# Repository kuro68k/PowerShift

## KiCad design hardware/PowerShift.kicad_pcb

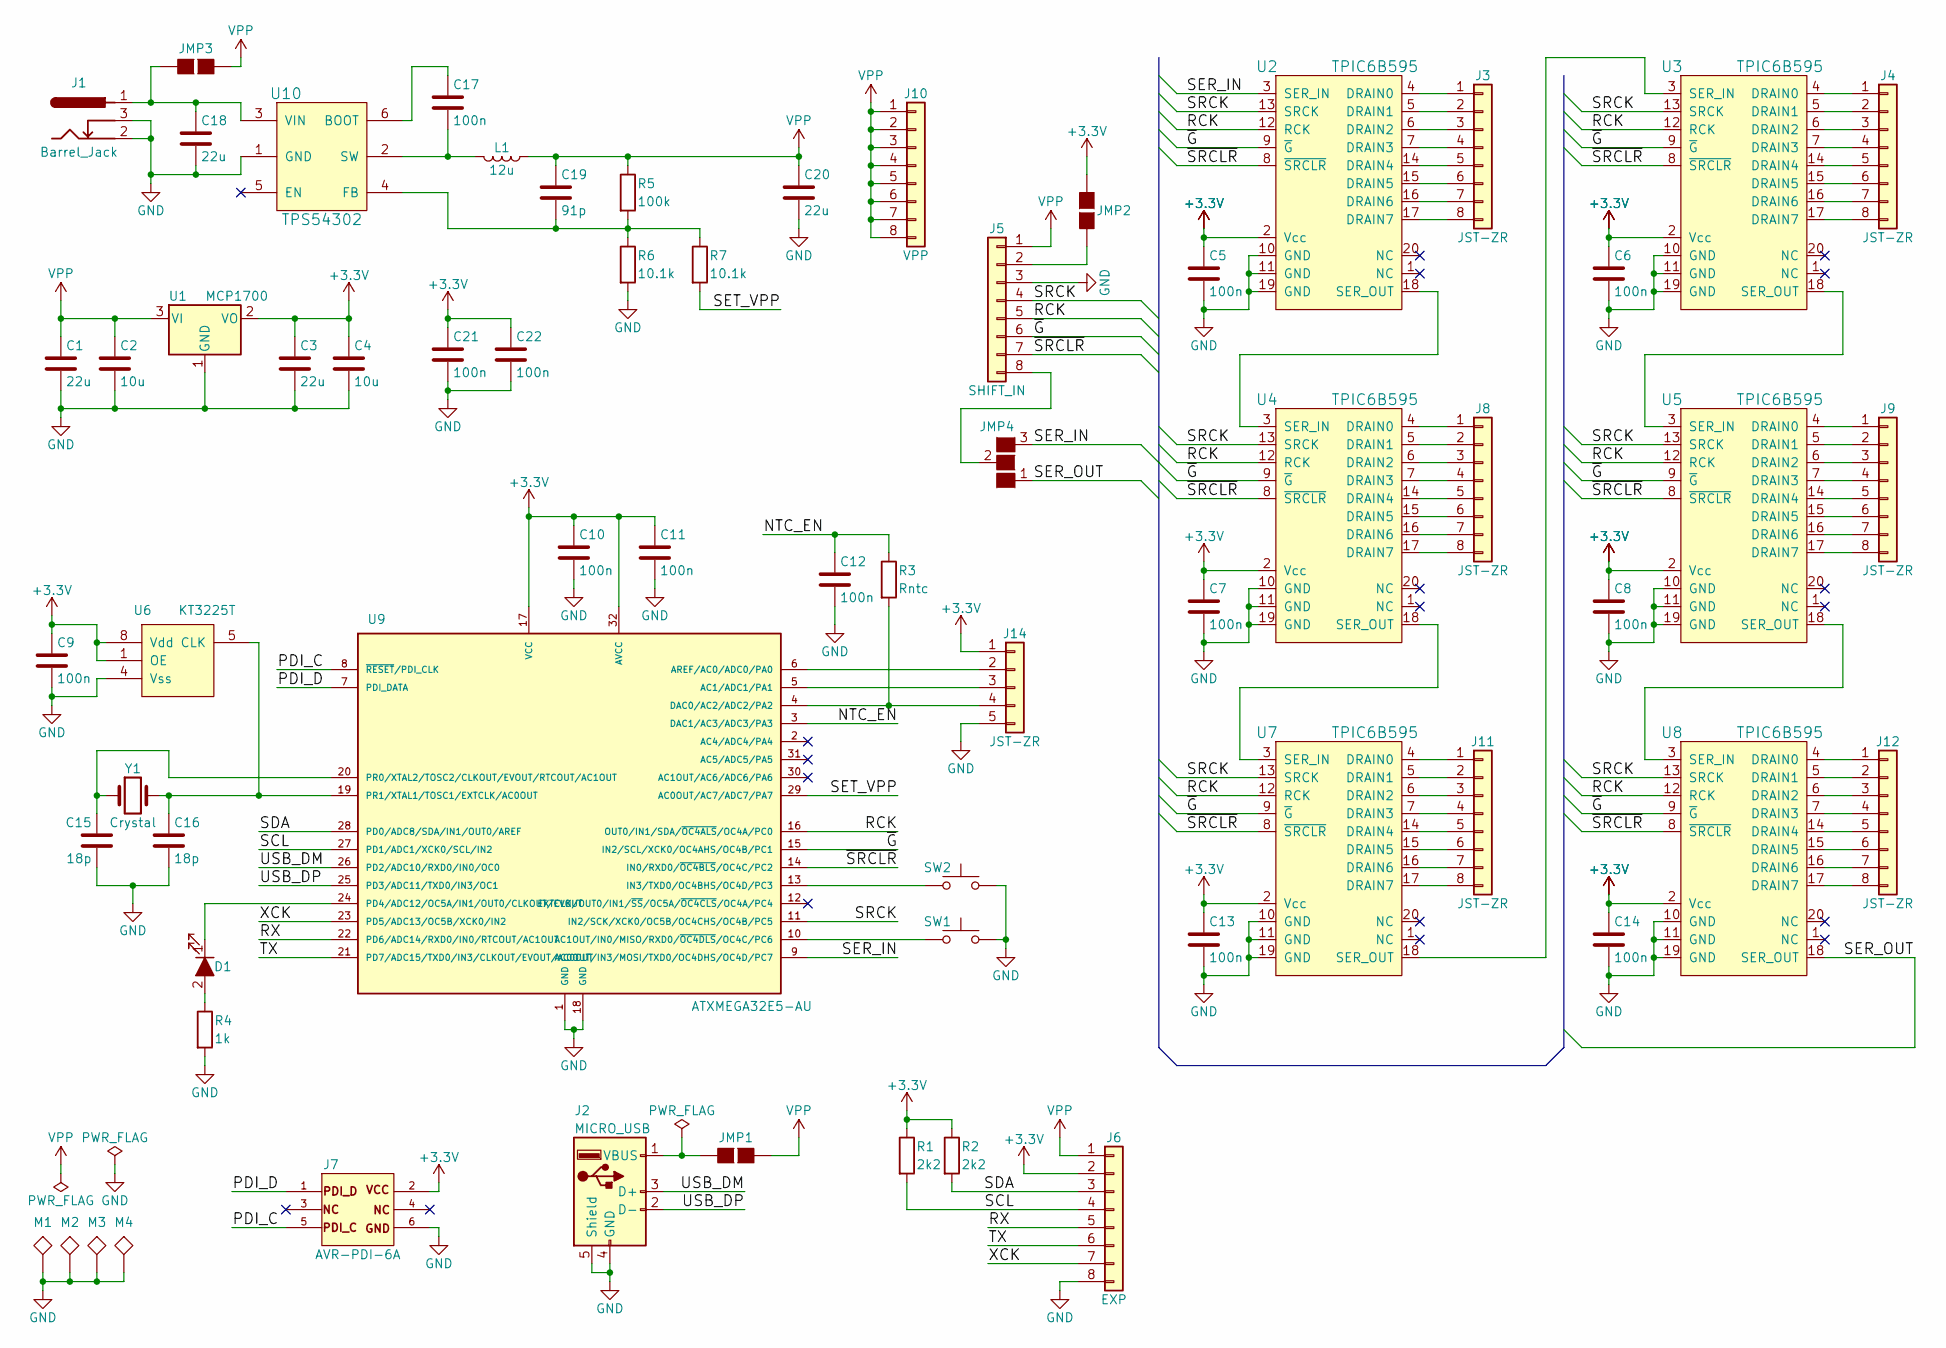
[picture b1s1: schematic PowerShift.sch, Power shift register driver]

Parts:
C1, C3, C18, C20: 22u; C_0805_HandSoldering
C2, C4: 10u; C_0603_HandSoldering
C5, C6, C7, C8, C9, C10, C11, C12, C13, C14, C17, C21, C22: 100n; C_0603_HandSoldering
C15, C16: 18p; C_0603_HandSoldering
C19: 91p; C_0603_HandSoldering
D1: LED_ALT; LED_0603_HandSoldering
J1: Barrel_Jack; DC_Jack_SMD_FC6814xS_6941
J2: MICRO_USB; Molex_47346-0001_Micro_USB_SMT
J3, J4, J8, J9, J11, J12: JST-ZR; B8B-ZR-SM4-TF
J5: SHIFT_IN; Pin_Header_Straight_1x08_Pitch2.54mm
J6: EXP; B8B-ZR-SM4-TF
J7: AVR-PDI-6A; Pin_Header_Angled_2x03_Pitch2.54mm
J10: VPP; B8B-ZR-SM4-TF
J14: JST-ZR; B5B-ZR-SM4-TF
JMP1, JMP2, JMP3: GS2
JMP4: GS3
L1: 12u; Bourns_SDR1307_14x14mm
M1, M2, M3, M4: TEST; MountingHole_2.7mm_M2.5_Pad
R1, R2: 2k2; R_0603_HandSoldering
R3: Rntc; R_0603_HandSoldering
R4: 1k; R_0603_HandSoldering
R5: 100k; R_0603_HandSoldering
R6, R7: 10.1k; R_0603_HandSoldering
SW1, SW2: SW_Push; Switch_FSM-JSM-Series
U1: MCP1700; SOT-23
U2, U3, U4, U5, U7, U8: TPIC6B595; SOIC-20W_7.5x12.8mm_Pitch1.27mm
U6: KT3225T
U9: ATXMEGA32E5-AU; TQFP-32_7x7mm_Pitch0.8mm
U10: TPS54302; SOT-23-6_Handsoldering
Y1: Crystal; Crystal_2pin_6x3.5_3.2x1.5_Multi

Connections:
+3V3: C3.1, C4.1, C5.1, C6.1, C7.1, C8.1, C9.1, C10.1, C11.1, C13.1, C14.1, C21.1, C22.1, J6.2, J7.2, J14.1, JMP2.1 (G1), R1.1, R2.1, U1.2 (VO), U2.2 (Vcc), U3.2 (Vcc), U4.2 (Vcc), U5.2 (Vcc), U6.1 (OE), U6.8 (Vdd), U7.2 (Vcc), U8.2 (Vcc), U9.17 (VCC), U9.32 (AVCC)
/NTC_EN: C12.1, R3.1, U9.3 (DAC1/AC3/ADC3/PA3)
/PDI_C: J7.5, U9.8 (~RESET~/PDI_CLK)
/PDI_D: J7.1, U9.7 (PDI_DATA)
/RCK: J5.5, U2.12 (RCK), U3.12 (RCK), U4.12 (RCK), U5.12 (RCK), U7.12 (RCK), U8.12 (RCK), U9.16 (OUT0/IN1/SDA/~OC4ALS~/OC4A/PC0)
/RX: J6.5, U9.22 (PD6/ADC14/RXD0/IN0/RTCOUT/AC1OUT)
/SCL: J6.4, R1.2, U9.27 (PD1/ADC1/XCK0/SCL/IN2)
/SDA: J6.3, R2.2, U9.28 (PD0/ADC8/SDA/IN1/OUT0/AREF)
/SER_IN: JMP4.3 (G3), U2.3 (SER_IN), U9.9 (AC0OUT/IN3/MOSI/TXD0/OC4DHS/OC4D/PC7)
/SER_OUT: JMP4.1 (G1), U8.18 (SER_OUT)
/SET_VPP: R7.2, U9.29 (AC0OUT/AC7/ADC7/PA7)
/SRCK: J5.4, U2.13 (SRCK), U3.13 (SRCK), U4.13 (SRCK), U5.13 (SRCK), U7.13 (SRCK), U8.13 (SRCK), U9.11 (IN2/SCK/XCK0/OC5B/OC4CHS/OC4B/PC5)
/TX: J6.6, U9.21 (PD7/ADC15/TXD0/IN3/CLKOUT/EVOUT/AC0OUT)
/USB_DM: J2.3 (D+), U9.26 (PD2/ADC10/RXD0/IN0/OC0)
/USB_DP: J2.2 (D-), U9.25 (PD3/ADC11/TXD0/IN3/OC1)
/XCK: J6.7, U9.23 (PD5/ADC13/OC5B/XCK0/IN2)
/~G: J5.6, U2.9 (~G), U3.9 (~G), U4.9 (~G), U5.9 (~G), U7.9 (~G), U8.9 (~G), U9.15 (IN2/SCL/XCK0/OC4AHS/OC4B/PC1)
/~SRCLR: J5.7, U2.8 (~SRCLR), U3.8 (~SRCLR), U4.8 (~SRCLR), U5.8 (~SRCLR), U7.8 (~SRCLR), U8.8 (~SRCLR), U9.14 (IN0/RXD0/~OC4BLS~/OC4C/PC2)
GND: C1.2, C2.2, C3.2, C4.2, C5.2, C6.2, C7.2, C8.2, C9.2, C10.2, C11.2, C12.2, C13.2, C14.2, C15.2, C16.2, C18.2, C20.2, C21.2, C22.2, J1.2, J1.3, J2.4 (GND), J2.5 (Shield), J5.3, J6.8, J7.6, J14.5, M1.1, M2.1, M3.1, M4.1, R4.2, R6.2, SW1.1, SW2.1, U1.1 (GND), U2.10 (GND), U2.11 (GND), U2.19 (GND), U3.10 (GND), U3.11 (GND), U3.19 (GND), U4.10 (GND), U4.11 (GND), U4.19 (GND), U5.10 (GND), U5.11 (GND), U5.19 (GND), U6.4 (Vss), U7.10 (GND), U7.11 (GND), U7.19 (GND), U8.10 (GND), U8.11 (GND), U8.19 (GND), U9.1 (GND), U9.18 (GND), U10.1 (GND)
unnamed: C15.1, U9.20 (PR0/XTAL2/TOSC2/CLKOUT/EVOUT/RTCOUT/AC1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), Y1.1
unnamed: C16.1, U6.5 (CLK), U9.19 (PR1/XTAL1/TOSC1/EXTCLK/AC0OUT), Y1.2
unnamed: C17.1, U10.6 (BOOT)
unnamed: C17.2, L1.2, U10.2 (SW)
unnamed: C18.1, J1.1, JMP3.1 (G1), U10.3 (VIN)
unnamed: C19.2, R5.2, R6.1, R7.1, U10.4 (FB)
unnamed: D1.1 (K), U9.24 (PD4/ADC12/OC5A/IN1/OUT0/CLKOUT/EVOUT)
unnamed: D1.2 (A), R4.1
unnamed: J2.1 (VBUS), JMP1.1 (G1)
unnamed: J3.1, U2.4 (DRAIN0)
unnamed: J3.2, U2.5 (DRAIN1)
unnamed: J3.3, U2.6 (DRAIN2)
unnamed: J3.4, U2.7 (DRAIN3)
unnamed: J3.5, U2.14 (DRAIN4)
unnamed: J3.6, U2.15 (DRAIN5)
unnamed: J3.7, U2.16 (DRAIN6)
unnamed: J3.8, U2.17 (DRAIN7)
unnamed: J4.1, U3.4 (DRAIN0)
unnamed: J4.2, U3.5 (DRAIN1)
unnamed: J4.3, U3.6 (DRAIN2)
unnamed: J4.4, U3.7 (DRAIN3)
unnamed: J4.5, U3.14 (DRAIN4)
unnamed: J4.6, U3.15 (DRAIN5)
unnamed: J4.7, U3.16 (DRAIN6)
unnamed: J4.8, U3.17 (DRAIN7)
unnamed: J5.2, JMP2.2 (G2)
unnamed: J5.8, JMP4.2 (G2)
unnamed: J8.1, U4.4 (DRAIN0)
unnamed: J8.2, U4.5 (DRAIN1)
unnamed: J8.3, U4.6 (DRAIN2)
unnamed: J8.4, U4.7 (DRAIN3)
unnamed: J8.5, U4.14 (DRAIN4)
unnamed: J8.6, U4.15 (DRAIN5)
unnamed: J8.7, U4.16 (DRAIN6)
unnamed: J8.8, U4.17 (DRAIN7)
unnamed: J9.1, U5.4 (DRAIN0)
unnamed: J9.2, U5.5 (DRAIN1)
unnamed: J9.3, U5.6 (DRAIN2)
unnamed: J9.4, U5.7 (DRAIN3)
unnamed: J9.5, U5.14 (DRAIN4)
unnamed: J9.6, U5.15 (DRAIN5)
unnamed: J9.7, U5.16 (DRAIN6)
unnamed: J9.8, U5.17 (DRAIN7)
unnamed: J11.1, U7.4 (DRAIN0)
unnamed: J11.2, U7.5 (DRAIN1)
unnamed: J11.3, U7.6 (DRAIN2)
unnamed: J11.4, U7.7 (DRAIN3)
unnamed: J11.5, U7.14 (DRAIN4)
unnamed: J11.6, U7.15 (DRAIN5)
unnamed: J11.7, U7.16 (DRAIN6)
unnamed: J11.8, U7.17 (DRAIN7)
unnamed: J12.1, U8.4 (DRAIN0)
unnamed: J12.2, U8.5 (DRAIN1)
unnamed: J12.3, U8.6 (DRAIN2)
unnamed: J12.4, U8.7 (DRAIN3)
unnamed: J12.5, U8.14 (DRAIN4)
unnamed: J12.6, U8.15 (DRAIN5)
unnamed: J12.7, U8.16 (DRAIN6)
unnamed: J12.8, U8.17 (DRAIN7)
unnamed: J14.2, U9.6 (AREF/AC0/ADC0/PA0)
unnamed: J14.3, U9.5 (AC1/ADC1/PA1)
unnamed: J14.4, R3.2, U9.4 (DAC0/AC2/ADC2/PA2)
unnamed: SW1.2, U9.10 (AC1OUT/IN0/MISO/RXD0/~OC4DLS~/OC4C/PC6)
unnamed: SW2.2, U9.13 (IN3/TXD0/OC4BHS/OC4D/PC3)
unnamed: U2.18 (SER_OUT), U4.3 (SER_IN)
unnamed: U3.3 (SER_IN), U7.18 (SER_OUT)
unnamed: U3.18 (SER_OUT), U5.3 (SER_IN)
unnamed: U4.18 (SER_OUT), U7.3 (SER_IN)
unnamed: U5.18 (SER_OUT), U8.3 (SER_IN)
VPP: C1.1, C2.1, C19.1, C20.1, J5.1, J6.1, J10.1, J10.2, J10.3, J10.4, J10.5, J10.6, J10.7, J10.8, JMP1.2 (G2), JMP3.2 (G2), L1.1, R5.1, U1.3 (VI)

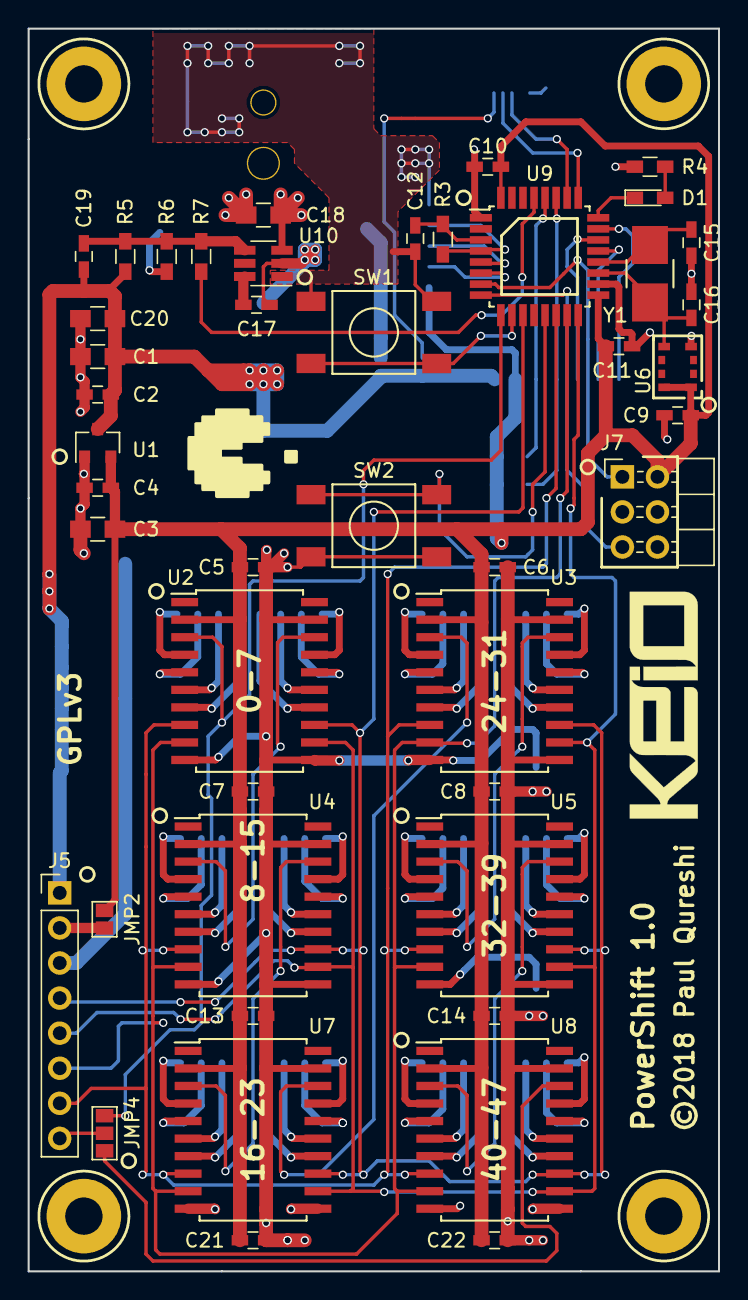
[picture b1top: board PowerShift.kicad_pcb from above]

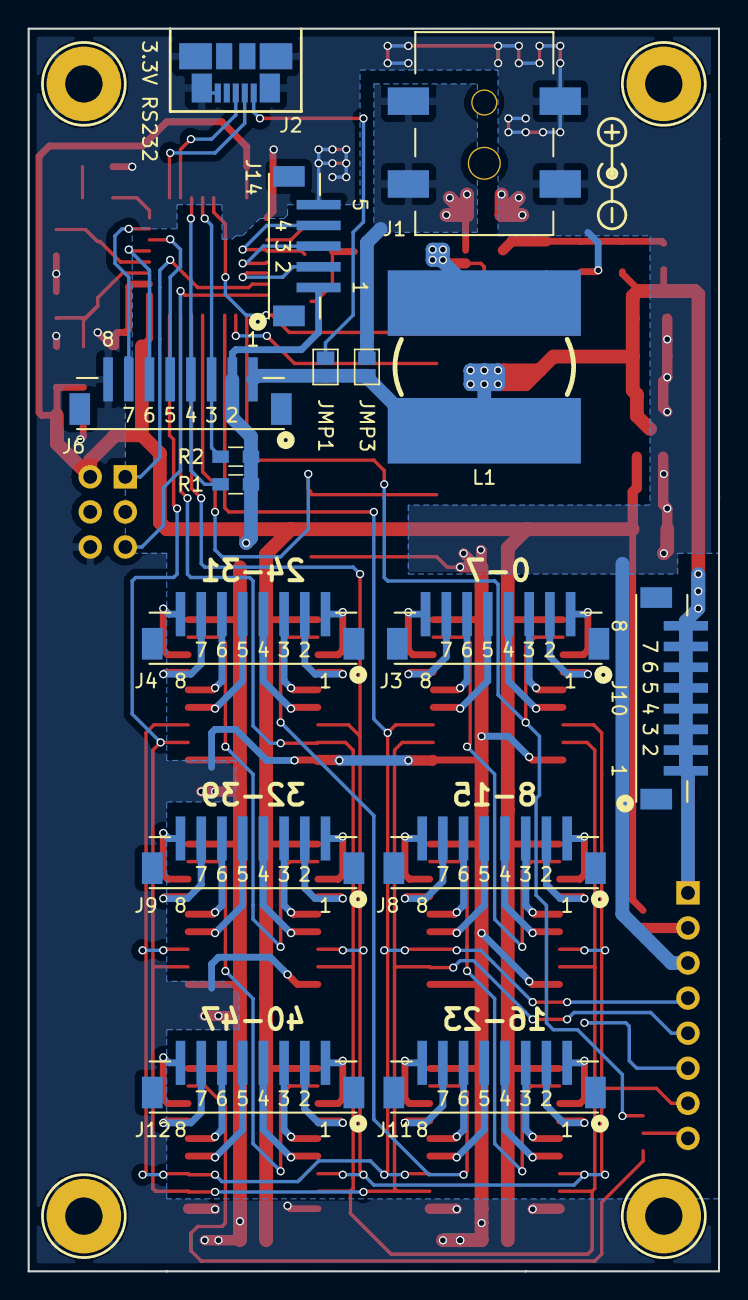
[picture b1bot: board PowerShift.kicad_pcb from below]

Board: 2 copper layers, 50.0 x 90.0 mm, 65 parts (16 on the bottom side), 89 nets.

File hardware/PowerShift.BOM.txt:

Title:      Power shift register driver
Date:       28/06/2018 16:40:15
Source:     PowerShift.sch
Revsision:  1.0

No.  Reference             Value           Footprint                       Precision

[ Capacitors, 5 values, X7R/X5R, 16V unless otherwise stated ]
------------------------------------------------------------------------------------
4    C1, C3, C18, C20      22u             0805                            
2    C2, C4                10u             0603                            
13   C5, C6, C7, C8, C9    100n            0603                            
     C10, C11, C12, C13
     C14, C17, C21, C22
2    C15, C16              18p             0603                            
1    C19                   91p             0603                            

[ Diodes, 1 value ]
------------------------------------------------------------------------------------
1    D1                    LED_ALT         0603                            

[ Connectors, 7 values ]
------------------------------------------------------------------------------------
1    J1                    Barrel_Jack     DC_Jack_SMD_FC6814xS_6941       
1    J2                    MICRO_USB       Molex_47346-0001_Micro_USB_SMT  
6    J3, J4, J8, J9, J11   JST-ZR          B8B-ZR-SM4-TF                   
     J12
1    J5                    SHIFT_IN        ...r_Straight_1x08_Pitch2.54mm  
2    J6, J10               SHIFT_IN        B8B-ZR-SM4-TF                   
1    J7                    AVR-PDI-6A      ...der_Angled_2x03_Pitch2.54mm  
1    J14                   JST-ZR          B5B-ZR-SM4-TF                   

[ JMP, 2 values ]
------------------------------------------------------------------------------------
3    JMP1, JMP2, JMP3      GS2             GS2                             
1    JMP4                  GS3             GS3                             

[ Inductors, 1 value ]
------------------------------------------------------------------------------------
1    L1                    12u             Bourns_SDR1307_14x14mm          

[ Resistors, 5 values, 1% unless otherwise stated ]
------------------------------------------------------------------------------------
2    R1, R2                2k2             0603                            
1    R3                    Rntc            0603                            
1    R4                    1k              0603                            
1    R5                    100k            0603                            
1    R6                    10.1k           0603                            

[ SW, 1 value ]
------------------------------------------------------------------------------------
2    SW1, SW2              SW_Push         Switch_FSM-JSM-Series           

[ Integrated Circuits, 5 values ]
------------------------------------------------------------------------------------
1    U1                    MCP1700         SOT-23                          
6    U2, U3, U4, U5, U7    TPIC6B595       ...-20W_7.5x12.8mm_Pitch1.27mm  
     U8
1    U6                    KT3225T         KT3225T                         
1    U9                    ATXMEGA32E5-AU  TQFP-32                         
1    U10                   TPS54302        SOT-23                          

[ Crystals, 1 value ]
------------------------------------------------------------------------------------
1    Y1                    Crystal         ...al_2pin_6x3.5_3.2x1.5_Multi

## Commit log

2018-06-24 RS232 expansion
2018-06-24 JST 5 pin common part
2018-06-24 Values
2018-06-24 ERC OK
2018-06-25 Step down regulator
2018-06-25 Buck reg bypass
2018-06-25 Footprints
2018-06-25 Test driver/header layout
2018-06-26 Additional shift reg caps
2018-06-26 PDI header to 1.27mm SMD
2018-06-26 Shift registers laid out
2018-06-26 MCU planning
2018-06-26 DC jack footprint
2018-06-26 Power supply layout
2018-06-26 Combined in/out header
2018-06-26 Mounting holes
2018-06-26 Display power header
2018-06-26 Aligned drivers
2018-06-26 Board outline
2018-06-26 All on board
2018-06-27 R/A PDI header footprint
2018-06-27 GND plane and 3V3 supply
2018-06-27 Nearly there
2018-06-27 All nets connected, DRC OK
2018-06-27 Silkscreen
2018-06-27 Top silk
2018-06-28 Buttons
2018-06-28 Corrected top silk for buttons
2018-06-28 Bottom silk
2018-06-28 Top silk fix
2018-06-28 Plot output
2018-06-28 Added BOM
2018-06-28 Datasheets
2018-06-28 Multi footprint crystal
2018-06-28 Corrected dimension marker
2018-06-28 Cleaned up schematic layout
2018-07-04 Added PDF of schematic
2018-07-04 Initial commit of clock firmware
2018-07-04 Silk on silk layers
2018-07-04 NTC measurement
2018-07-04 Keio logo on silk layer
2018-07-05 Pin 1 marker for U10
2018-07-05 Silkscreen for U6
2018-07-08 Added Vpp voltage switch
2018-07-09 Updated PDF schematic
2018-07-09 Brightness control
2018-07-09 Test mode

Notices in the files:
hardware/PowerShift.kicad_pcb:
Licence: GPLv3
GPLv3
©2018 Paul Qureshi
